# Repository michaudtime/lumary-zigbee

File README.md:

# Lumary Zigbee Controller

Replaces the Tuya WiFi controller inside a **Lumary 6" RGBAI recessed light** with an **ESP32-H2 Zigbee controller**, enabling:

- Direct Zigbee binding to Inovelli Blue Series switches (hub-independent on/off, dimming, scene control)
- 6 built-in lighting effects on the accent ring, with per-scene parameters stored on-device
- Zigbee OTA firmware updates via Zigbee2MQTT

## Hardware

| Component | Part |
|---|---|
| Controller | **lumary-brain rev A** — custom ESP32-H2-MINI-1 board, drop-in for the stock `KOK-AH-A172C` (see `hardware/`) |
| Target light | [Lumary Smart RGBAI Recessed Light 6"](https://www.lumarysmart.com/products/lumary-smart-recessed-light-with-gradient-auxiliary-light) |
| Switch | [Inovelli Blue Series 2-1 Zigbee](https://inovelli.com/products/zigbee-matter-blue-series-smart-2-1-on-off-dimmer-switch) |

### The two light sources

The fixture has two independent sources, and the firmware drives them as **two separate Zigbee
endpoints**, so Home Assistant sees two independent light entities rather than one:

| Source | Hardware | Driven by |
|---|---|---|
| Outer "gradient" ring | 62-pixel 5 V 3535 **RGBIC** strip, 3 colour bytes/pixel (no white die) | One data line, NZR over SPI |
| Inner white ring | 96 LEDs, 12 series × 4 parallel per colour, 2700 K + 6500 K | Two low-side PWM channels steering the driver's 380 mA |

The external `L-SD8E1` driver supplies **36.63 V constant-current** (inner white anode) and **4.7 V** (ring + logic). The board never sources the white current — it gates and steers it.

| Entity | Endpoint | Controls |
|---|---|---|
| `light.<name>_downlight` | 1 | on/off, brightness, colour temperature 2700–6500 K |
| `light.<name>_ring` | 2 | on/off, brightness, xy colour, the six effects |

> **Upgrading an already-paired fixture:** adding the second endpoint changes the device
> descriptor, and Zigbee2MQTT caches endpoints from the interview, so an already-paired fixture
> must be **re-interviewed** (Z2M frontend → device → Re-interview, or publish to
> `zigbee2mqtt/bridge/request/device/interview`) before the ring entity works. This has never been
> observed on hardware, so exactly what you'll see beforehand is unconfirmed either way -- expect
> the ring entity to be missing entirely, or present but unresponsive, until the re-interview is
> done. Newly paired fixtures just work.
>
> It is also no longer easy to check: both fixtures in service have already crossed this descriptor
> change, and a fixture that has crossed it cannot show you the before. Settling it would mean
> deliberately pairing a board on pre-2.0.0 firmware and upgrading it while watching -- worth doing
> when the remaining rev A boards are brought up, or this hedge should simply stay as written.

### Wiring (rev A board)

| ESP32-H2 Pin | Signal | Destination |
|---|---|---|
| GPIO 11 (SPI2 MOSI) | Ring data → 3.3→4.7 V buffer | `CN1.DIM` (ring DIN) |
| GPIO 4 | PWM cold white → Q1 gate | `CN1.CW-` (6500 K return) |
| GPIO 5 | PWM warm white → Q2 gate | `CN1.WW-` (2700 K return) |
| GPIO 9 | BOOT button | Bench download / BLE OTA |

> **Pin note:** GPIO 2/3/8/9/25 are ESP32-H2 strapping pins. The white PWM channels use GPIO 4/5 on rev A so the MOSFET gate pulldowns can't hold a strapping pin low at reset — the Super Mini prototype's GPIO 2/3 assignment does not carry over.

> **Level shifting:** the ring runs on the 4.7 V rail, so its data line is buffered up from 3.3 V by a `74AHCT1G125` (AHCT accepts 3.3 V as a logic high).

## Why SPI instead of RMT for the ring?

On ESP32-H2, the RMT peripheral conflicts with the Zigbee radio. Instead, SPI2 bit-encodes the single-wire NZR protocol: each NZR bit becomes 3 SPI bits (`1 → 110`, `0 → 100`) at 2.4 MHz, producing a valid 800 kHz signal on MOSI. The encoder lives in `src/pixel_encode.h`, deliberately free of ESP-IDF headers so it can be unit-tested on the host.

## Built-in Effects

These belong to the **Accent Ring** entity only — the Downlight has no effects, just on/off,
brightness and colour temperature.

| # | Name | Description |
|---|---|---|
| 1 | Warm Gradient | Warm→cool sweep rotating around the ring |
| 2 | Color Gradient | Multi-hue gradient rotating around ring |
| 3 | Breathing | Outer ring pulses in/out |
| 4 | Color Cycle | Full HSV hue rotation |
| 5 | Chase | Single lit segment travels around ring |
| 6 | Nightlight | Dim warm white outer ring only |

> **Changed in this version:** `static_white` and `static_color` are gone from the effect list.
> White is now the separate Downlight entity, and a solid ring colour is `effect: none` with a
> colour set. Automations naming either of the two removed effects need updating. Stored scenes
> are reseeded automatically — the NVS schema version bump discards the old indices rather than
> misreading them.

## Switch Control (Hub-Independent)

| Inovelli action | Behavior |
|---|---|
| 1× tap | On/Off |
| Hold up/down | Brightness |
| 2× tap up | Next effect — **via hub automation**, see below |
| 2× tap down | Previous effect — **via hub automation** |

On/off and dimming use direct Zigbee binding — **no hub required**, and they keep working if the
coordinator is down. With two fixture endpoints, the switch binds to both:

```
Bind from the Inovelli's endpoint 2 (the paddle) to BOTH fixture endpoints,
clusters genOnOff and genLevelCtrl:

  switch ep2 -> fixture ep1   (downlight)
  switch ep2 -> fixture ep2   (accent ring)
```

One tap down turns both sources off; one tap up brings both back at their own levels and colours.
This works because the Inovelli sends discrete `On`/`Off` rather than `Toggle` — verified on the
hardware. Under `Toggle`, two endpoints that had drifted into different states would diverge
further on every tap instead of converging. "Downlight only" is a Home Assistant action rather
than a switch action; remove the second binding if you would rather the ring ignored the switch.

> **Effect stepping is not hub-independent, and cannot be.** The Inovelli's multi-tap events are
> manufacturer-specific and go to the coordinator rather than to a bound light, so nothing the
> light does could make 2× tap work over pure binding. The automation reads the current
> `effect_select` and writes the next one. Not yet verified end to end (plan Task 6.4).

## Selecting an effect

Effect selection rides a **manufacturer-specific cluster (`0xFC00`)**, because nothing standard can
carry it: the Scenes cluster stores colour and level but knows nothing about an effect type, and
the Identify trigger-effects have no hook in the Arduino Zigbee library.

Install [`z2m/lumary-brain-revA.js`](z2m/lumary-brain-revA.js) into Z2M's `data/external_converters/`
and restart. Without the converter the light still works normally — the effects are simply
unreachable.

The converter exposes the effects as the **Accent Ring entity's native Home Assistant effect
list**, so they appear in the effect dropdown of the ring's light card itself rather than as a
separate entity:

```yaml
service: light.turn_on
target: {entity_id: light.lumary_kitchen_ring}
data: {effect: color_cycle}
```

That also means HA scene snapshots capture the running effect, and voice assistants can select one.
The current effect reads back as `state_attr('light.lumary_kitchen_ring', 'effect')`.

| Value | Meaning |
|---|---|
| `warm_gradient` … `nightlight` | One of the six built-in effects, in `EffectType` order |
| `none` | Not running an effect — showing a plain colour |

Setting a colour on the ring **exits the effect** and shows that colour instead, which reads back
as `none`. Selecting `none` does the same thing without changing the colour. Brightness continues
to scale whatever effect is running.

The selected effect persists across power cuts (NVS); `none` deliberately does not, so a power
cycle comes back to the stored effect.

> The Identify trigger-effects that Z2M's stock `effect` dropdown drives (`blink`, `breathe`,
> `okay`, …) are **switched off** in the converter, along with `power_on_behavior`. Both are on by
> default in `light()`, and this firmware implements neither — leaving them on would put controls in
> the light card that quietly do nothing. See `effect: false` / `powerOnBehavior: false` there.

> **Stepping through effects from the wall switch** is done by a hub automation, not by the light:
> read the current effect and set the next one. The Inovelli's multi-tap events go to the
> coordinator rather than to a bound light, so a hub is in the loop regardless.

Scene *storage* exists — 16 NVS slots, seeded with the defaults in `src/effect_params.h` — but
editing them is **not implemented**. There is no Add Scene support; `scene_store_save()` is only
called to seed defaults at first boot. Changing an effect's colour, speed or brightness
permanently is a future change.

## OTA Updates

> **Re-flashing a fixture that was already paired?** See "Upgrading an already-paired fixture"
> above — after this update it needs a Z2M **re-interview** before the ring entity works, or the
> upgrade will look broken even though it succeeded.

**Primary:** Zigbee OTA via Zigbee2MQTT.

Three things must all be true, and each one fails differently:

| Requirement | Symptom when missing |
|---|---|
| Firmware registers an OTA client | Device never asks; nothing in the Z2M log |
| Converter declares `ota: true` | **No `update` entity at all** in Home Assistant |
| Z2M can find the image via an index | Update entity exists; update fails `No image currently available` |

> **Z2M does not discover firmware by scanning a folder.** Copying a `.zigbee` file into `data/ota/`
> accomplishes nothing on its own — Z2M reads an *index* that describes the image, pointed at by
> `ota.zigbee_ota_override_index_location` in `configuration.yaml`. `scripts/gen-ota-index.py`
> generates one; see "Building an OTA image" below.

> **`ota` is a definition property, not a modern extend.** There is no `m.ota()` in
> zigbee-herdsman-converters, and using one makes Z2M reject the entire converter as invalid at load
> time. It goes on the definition object alongside `onEvent`.

**There is no fallback.** A BLE OTA path was planned — `PIN_BLE_OTA_BUTTON` is still defined in
`src/config.h` — but it was never implemented, and nothing references that pin. Do not count on it
for a fixture already in the ceiling: if Zigbee OTA cannot reach a light, the only recovery is
physical access to the USB port. Getting Zigbee OTA verified from an installed location is
consequently the gate on signing off the board (plan task 6.4), not a nice-to-have.

### Scheduled updates and automatic recovery (2.1.0 and later)

**Start updates with *schedule*, not *update*:**

```
topic:   zigbee2mqtt/bridge/request/device/ota_update/schedule
payload: {"id": "Loft Overhead Light"}
```

> **This means not using the Install button on Home Assistant's update card.** That button is the
> `ota_update/update` path: Zigbee2MQTT pushes an image notify at the fixture and waits for it to
> answer, which for a fixture a floor away from the coordinator typically ends in
> `OTA update of '<name>' failed (Device didn't respond to OTA request)` — a failure that says
> nothing about the image or the index. `schedule` parks the request instead and lets the fixture
> collect it on its own next query, which is what the recovery loop below is built around. Seen
> 2026-09-21 on the loft fixture: Install failed this way, the same image then installed from a
> schedule.
>
> `check`, `update` and `schedule` share one per-device lock, so a `schedule` sent while either of
> the others is still running is rejected with
> `OTA update or check for update already in progress for '<name>'`. Wait for the first to finish
> and send it again.

The fixture queries for an image shortly after it joins the network at boot, then hourly. A
scheduled update starts on whichever of those queries comes next, and Zigbee2MQTT keeps it
scheduled if it fails. Combined with the firmware's recovery this makes an update self-healing:

1. If a download aborts, or stalls for 3 minutes, the fixture saves its light state, restarts
   (the light blinks for about a second, then comes back as it was), and rejoins.
2. On rejoin it queries for an image, and the still-scheduled update starts again from the
   beginning.
3. When it succeeds, the fixture restarts into the new version and comes back **off** -- light
   state is only carried across a recovery restart, not across the update's own restart -- and
   Zigbee2MQTT clears the schedule.

The restart itself backs off on repeated recoveries: the first two consecutive recoveries restart
at once, but from the third the restart waits 5 minutes, doubling each time up to an hour, so an
image that fails the same way every time cannot make a fixture blink every few seconds. It never
stops retrying on its own -- `unschedule` is what stops it.

The restart is required: the Arduino Zigbee library never resets its OTA state after an abort, so
without it every retry fails `INVALID_IMAGE` two blocks in. To stop a fixture retrying an image that
can never succeed, send the same payload to `.../ota_update/unschedule`. Each recovery is logged on
the serial console with a running count.

**Fixtures on firmware older than 2.1.0** have no automatic recovery: after a failed update, power-
cycle the fixture before retrying. From Home Assistant, via its Inovelli switch: turn the switch
off, set its Smart Bulb Mode to `Disabled` (the switch is off, so the load loses power), wait ~15 s,
then set Smart Bulb Mode back to `Smart Bulb Mode` (full power returns and the fixture boots).

### Building an OTA image

The device registers an OTA client at startup and queries for an image once it
joins, then hourly. The coordinator only offers images numbered **above** the
running version, so the version block in `src/version.h` must be bumped and the
same `ZB_FW_VERSION` passed as `--file-version` below — if they disagree, the
update silently never appears.

> **The tool was renamed and its CLI changed.** Espressif's `tools/ota_image_tool.py`
> is gone; it is now `tools/image_builder_tool/image_builder_tool.py`, it takes short
> flags rather than the old long ones, and the firmware is supplied as a `--tag`
> sub-element rather than a positional argument. There is no `create` subcommand, and
> the output filename is generated for you rather than given. Verified 2026-08-18.

```bash
# Get the tool
mkdir -p build/ota && curl -sSL -o build/ota/image_builder_tool.py   https://raw.githubusercontent.com/espressif/esp-zigbee-sdk/main/tools/image_builder_tool/image_builder_tool.py

# Build firmware (bump the version block in src/version.h first)
pio run -e esp32h2

# Wrap as an OTA image. -m/-i come from src/config.h (ZB_MANUFACTURER_CODE,
# ZB_IMAGE_TYPE); -v must equal ZB_FW_VERSION. Tag 0x0000 is the upgrade image.
cd build/ota && python image_builder_tool.py   -m 0x1001   -i 0x0001   -v 0x02000000   -s 2   -g "LumaryZigbee"   --tag 0x0000 ../../.pio/build/esp32h2/firmware.bin
```

The output is named from the three identifiers rather than chosen — for the values above,
`1001-0001-02000000-ota-file.zigbee`.

Then generate the index Z2M actually reads. It takes the manufacturer code, image type, file version
and header string out of the image itself rather than from arguments, so the index cannot disagree
with the file it describes:

```bash
python scripts/gen-ota-index.py build/ota/1001-0001-02000000-ota-file.zigbee
```

Copy **both** the `.zigbee` image and the generated `index.json` into Z2M's `data/ota/` folder, then
point `configuration.yaml` at the index and restart Z2M:

```yaml
ota:
  zigbee_ota_override_index_location: ota/index.json
```

Both paths are relative to the **Z2M data directory** — the index's own location, and the `url`
inside it naming the image. Verified end to end 2026-08-18 against Z2M 2.13.0: no http(s) URL and no
absolute path is needed for a locally served image.

> **The `url` is relative to the data directory, not to the index that contains it.** With the
> layout above the index lives at `data/ota/index.json` and the image sits beside it, so the `url`
> still needs the `ota/` prefix — `ota/foo.zigbee`, not `foo.zigbee`. `gen-ota-index.py` adds it.
>
> Getting this wrong is worth recognising, because it does not look like a path problem.
> `ota_update/check` reads index *metadata* only, so it reports `update_available: true` and Home
> Assistant offers the update quite happily. Only `ota_update/update` opens the file, and it reports
> the failure as **`No image currently available`** — the same message you get with no index at all.
> The real cause appears only in Z2M's debug log:
>
> ```
> zh:controller:ota: Reading firmware image from 'foo.zigbee'
> ENOENT: no such file or directory, open '/config/zigbee2mqtt/foo.zigbee'
> ```

Z2M caches the last OTA check, so after installing an index it will keep reporting the device as up
to date until it re-checks — on the next device announce, hourly, or immediately if you ask:

```
topic:   zigbee2mqtt/bridge/request/device/ota_update/check
payload: {"id": "Overhead light test"}
```

For a one-off test you can skip the index entirely and name the file in the update request, which is
useful for confirming the image itself is good before troubleshooting configuration:

```
topic:   zigbee2mqtt/bridge/request/device/ota_update/update
payload: {"id": "Overhead light test", "url": "ota/1001-0001-02000000-ota-file.zigbee"}
```

`build/` is git-ignored, so neither the tool, the image, nor the index is committed.

## Build & Flash

> **Re-flashing a fixture that was already paired?** See "Upgrading an already-paired fixture"
> above — after this update it needs a Z2M **re-interview** before the ring entity works, or the
> upgrade will look broken even though it succeeded.

> **Windows:** run `pio` from **PowerShell or cmd**, not Git Bash. This platform
> version installs its toolchain via `idf_tools.py`, which aborts with
> `ERROR: MSys/Mingw is not supported` under Git Bash. Building also needs
> Windows long-path support enabled (`LongPathsEnabled = 1`).
>
> `--target upload` fails differently and much more confusingly under Git Bash:
> esptool's progress bar is drawn with box-drawing characters, stdout falls back
> to **cp1252**, and the whole upload dies on `UnicodeEncodeError: 'charmap'
> codec can't encode characters` — after sitting silent for ~6 minutes, with the
> traceback replacing whatever the real error was. The board is fine; nothing was
> written. From PowerShell the same flash takes ~18 s. If you must run it from a
> shell with a non-UTF-8 codepage, `chcp 65001` and `PYTHONIOENCODING=utf-8`
> clear it (observed 2026-09-21).

```bash
# Install PlatformIO CLI if needed
pip install platformio

# Build
pio run -e esp32h2

# Flash
pio run -e esp32h2 --target upload

# Serial monitor
pio device monitor
```

## Project Structure

```
src/
  config.h          — Pin definitions, constants
  color.h           — CRGB struct, HSV conversion, color math
  pixel_encode.h    — NZR-over-SPI bit encoder (hardware-free, unit-tested)
  led_driver.h/.cpp — SPI2 ring driver + LEDC CW/WW PWM
  effect_params.h   — EffectType enum, EffectParams struct
  effects.h/.cpp    — 6 effect implementations + lookup table
  scene_store.h/.cpp — NVS scene persistence
  zigbee_light.h/.cpp — Zigbee clusters for both endpoints, and the OTA client
  brightness.h      — CIE 1931 lightness curve, generated tables
  main.cpp          — Setup, loop, watchdog
test/
  test_brightness/   — Host unit tests for the perceptual curve
  test_identify/     — Host unit tests for the identify overlay
  test_light_state/  — Host unit tests for the Zigbee -> fixture translation
  test_pixel_encode/ — Host unit tests for pixel encoding + color math
  test_version/      — Host unit tests for the version block
z2m/
  lumary-brain-revA.js — Z2M external converter
  test/             — Converter tests (stubbed, `node z2m/test/converter.test.mjs`)
hardware/
  kicad/            — Board design (build_board.py generates the .kicad_pcb)
  bom.csv, calcs.md, schematic-nets.md
docs/
  spec.md           — Hardware + software design specification
  plan.md           — Implementation plan
  superpowers/      — Board replacement spec, plan, and Phase 0 measurements
```

## Tests

Hardware-independent logic (pixel encoding, colour math) has host-side unit tests:

```bash
scripts\run-native-tests.bat
```

> PlatformIO's `platform = native` expects a gcc toolchain; this script compiles the
> same tests with the MSVC Build Tools that are installed instead. `pio test -e native`
> works as-is on a machine with gcc.

The Z2M converter has its own suite, covering the effect names, their wire indices and the
exposes Home Assistant discovers from them. It stubs the `zigbee-herdsman-converters` imports,
so it needs nothing installed but Node:

```bash
node z2m/test/converter.test.mjs
```

## Status

- [x] Design spec
- [x] Implementation plan
- [x] Task 1: Project scaffold
- [x] Task 2: Color utilities
- [x] Task 3: LED driver
- [x] Task 4: Scene storage
- [x] Task 5: Effects engine
- [x] Task 6: Zigbee basics
- [x] Task 7: Zigbee color + effect selection
- [x] Task 8: Zigbee OTA
- [ ] Task 9: BLE OTA fallback -- won't do (decided 2026-08-19); see "OTA Updates" above
- [ ] Task 10: Integration + validation -- bench-verified end to end
      (`docs/superpowers/plans/2026-08-18-bench-verification.md`, §§1-9), and **signed off from an
      installed ceiling location 2026-09-19**: binding to the Inovelli confirmed from the loft at
      LQI 126-138, and a real over-the-air update completed from there (Task 6.4 in
      `docs/superpowers/plans/2026-08-01-brain-replacement-board.md`). Still open: the
      already-paired-fixture upgrade path -- see the note under "Two entities" above, which now
      needs a fixture deliberately left on pre-2.0.0 firmware to observe at all
      (RSSI, thermals, a real OTA from there)

## License

MIT

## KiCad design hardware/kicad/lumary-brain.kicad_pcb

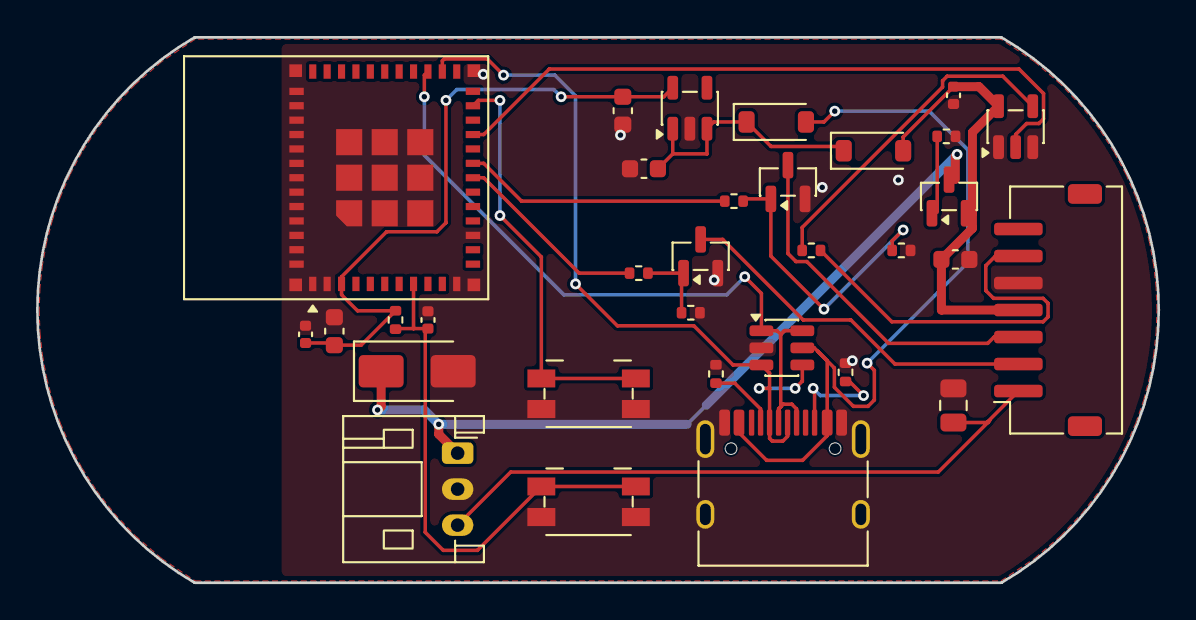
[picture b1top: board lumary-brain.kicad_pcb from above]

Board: 2 copper layers, 62.3 x 30.3 mm, 32 parts (0 on the bottom side), 23 nets.

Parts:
C1: 10uF/50V; C_0805_2012Metric
C2, C4, C5: 10uF; C_0603_1608Metric
C3: 1uF; C_0603_1608Metric
C6, C7: 100nF; C_0402_1005Metric
C8: 1uF; C_0402_1005Metric
D1, D2: B5819W; D_SOD-123
D3: SMAJ5.0A; D_SMA
J1: PWR_IN; JST_PH_S3B-PH-K_1x03_P2.00mm_Horizontal
J2: CN1; JST_ZH_S7B-ZR-SM4A-TF_1x07-1MP_P1.50mm_Horizontal
J3: USB-C; USB_C_Receptacle_HRO_TYPE-C-31-M-12
Q1, Q2: NMOS_60V; SOT-23
Q3: AO3401A; SOT-23
R1, R2: 100R; R_0402_1005Metric
R3, R4, R9: 100k; R_0402_1005Metric
R5: 200R; R_0402_1005Metric
R6: 10k; R_0402_1005Metric
R7, R8: 5.1k; R_0402_1005Metric
SW1: BOOT; Panasonic_EVQPUJ_EVQPUA
SW2: EN; Panasonic_EVQPUJ_EVQPUA
U1: ESP32-H2-MINI-1-N4; ESP32-C6-MINI-1
U2: ME6211C33M5G; SOT-23-5
U3: 74AHCT1G125; SOT-23-5
U4: USBLC6-2SC6; SOT-23-6

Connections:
+3V3: C2.1, C5.1, C6.1, R6.2, U1.3, U2.5
+4V7: C4.1, C7.1, D1.2, J2.4, Q3.2, U3.5
+4V7_IN: D3.1, J1.1, Q3.3
+36V: C1.1, J1.3, J2.1
CC1: J3.A5, R7.1
CC2: J3.B5, R8.1
CW_GATE: Q1.1, R1.2, R3.1
CW_PWM: R1.1, U1.18
CW_RET: J2.2, Q1.3
EN: C8.1, R6.1, SW2.1, U1.8
GND: C1.2, C2.2, C3.2, C4.2, C5.2, C6.2, C7.2, C8.2, D3.2, J1.2, J2.5, J3.A1, J3.A12, J3.B1, J3.B12, J3.SH, Q1.2, Q2.2, R3.2, R4.2, R7.2, R8.2, R9.2, SW1.2, SW2.2, U1.1, U1.2, U1.11, U1.14, U1.36, U1.37, U1.38, U1.39, U1.40, U1.41, U1.42, U1.43, U1.44, U1.45, U1.46, U1.47, U1.48, U1.49, U1.50, U1.51, U1.52, U1.53, U2.2, U3.1, U3.3, U4.2
IO9: SW1.1, U1.23
LDO_IN: C3.1, D1.1, D2.1, U2.1, U2.3
Q3_GATE: Q3.1, R9.1
RING_BUF_OUT: R5.1, U3.4
RING_DATA: J2.6, R5.2
RING_DATA_3V3: U1.21, U3.2
USB_DM: J3.A7, J3.B7, U1.26, U4.3, U4.4
USB_DP: J3.A6, J3.B6, U1.27, U4.1, U4.6
VBUS: D2.2, J3.A4, J3.A9, J3.B4, J3.B9, U4.5
WW_GATE: Q2.1, R2.2, R4.1
WW_PWM: R2.1, U1.19
WW_RET: J2.3, Q2.3

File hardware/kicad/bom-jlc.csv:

Comment,Designator,Footprint,LCSC Part #
10uF 50V,C1,0805,C440198
10uF 10V+,"C2,C4,C5",0603,C19702
1uF,C3,0603,C15849
100nF,"C6,C7",0402,C1525
1uF,C8,0402,C52923
B5819W SL,"D1,D2",SOD-123,C8598
SMAJ5.0A,D3,SMA,C113952
S3B-PH-K-S(LF)(SN),J1,JST-PH-3,C157929
S7B-ZR-SM4A-TF(LF)(SN),J2,ZH-7-SIDE,C5118704
TYPE-C-31-M-12 USB-C,J3,USB-C-16P,C165948
N-MOSFET 60V logic-level,"Q1,Q2",SOT-23,C347492
AO3401A,Q3,SOT-23,C15127
100R,"R1,R2",0402,C25076
100k,"R3,R4,R9",0402,C25741
200R,R5,0402,C25087
10k,R6,0402,C60489
5.1k,"R7,R8",0402,C25905
Tact switch EVQPUJ/EVQPUA,"SW1,SW2",SMD-4.7x3.5,C128539
ESP32-H2-MINI-1-N4,U1,ESP32-H2-MINI-1,C18203134
ME6211C33M5G-N,U2,SOT-23-5,C82942
SN74AHCT1G125DBVR,U3,SOT-23-5,C7484
USBLC6-2SC6,U4,SOT-23-6,C7519

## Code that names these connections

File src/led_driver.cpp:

#include "led_driver.h"
#include "pixel_encode.h"
#include "driver/spi_master.h"
#include "driver/ledc.h"

static spi_device_handle_t s_spi;
static uint8_t s_spi_buf[RING_SPI_BUF_SIZE];

void led_driver_init() {
    spi_bus_config_t bus = {};
    bus.mosi_io_num    = PIN_RING_DATA;
    bus.miso_io_num    = -1;
    bus.sclk_io_num    = PIN_RING_CLK_DUMMY;
    bus.quadwp_io_num  = -1;
    bus.quadhd_io_num  = -1;
    bus.max_transfer_sz = RING_SPI_BUF_SIZE;
    ESP_ERROR_CHECK(spi_bus_initialize(SPI2_HOST, &bus, SPI_DMA_CH_AUTO));

    spi_device_interface_config_t dev = {};
    dev.clock_speed_hz = RING_SPI_CLK_HZ;
    dev.mode           = 0;
    dev.spics_io_num   = -1;
    dev.queue_size     = 1;
    ESP_ERROR_CHECK(spi_bus_add_device(SPI2_HOST, &dev, &s_spi));

    ledc_timer_config_t timer = {};
    timer.speed_mode      = LEDC_LOW_SPEED_MODE;
    timer.timer_num       = LEDC_TIMER_0;
    timer.duty_resolution = PWM_RESOLUTION;
    timer.freq_hz         = PWM_FREQ_HZ;
    timer.clk_cfg         = LEDC_AUTO_CLK;
    ESP_ERROR_CHECK(ledc_timer_config(&timer));

    ledc_channel_config_t cw = {};
    cw.gpio_num   = PIN_CW_PWM;
    cw.speed_mode = LEDC_LOW_SPEED_MODE;
    cw.channel    = PWM_CHANNEL_CW;
    cw.timer_sel  = LEDC_TIMER_0;
    cw.duty       = 0;
    ESP_ERROR_CHECK(ledc_channel_config(&cw));

    ledc_channel_config_t ww = cw;
    ww.gpio_num = PIN_WW_PWM;
    ww.channel  = PWM_CHANNEL_WW;
    ESP_ERROR_CHECK(ledc_channel_config(&ww));
}

void led_driver_show(const CRGB* leds, uint16_t count) {
    memset(s_spi_buf, 0, RING_SPI_LEAD_BYTES);
    pixel_encode(leds, count, s_spi_buf + RING_SPI_LEAD_BYTES,
                 RING_SPI_BUF_SIZE - RING_SPI_LEAD_BYTES);
    spi_transaction_t t = {};
    t.length    = RING_SPI_BUF_SIZE * 8;
    t.tx_buffer = s_spi_buf;
    spi_device_polling_transmit(s_spi, &t);
}

void led_driver_set_cw(uint16_t duty) {
    ledc_set_duty(LEDC_LOW_SPEED_MODE, PWM_CHANNEL_CW, duty > PWM_DUTY_MAX ? PWM_DUTY_MAX : duty);
    ledc_update_duty(LEDC_LOW_SPEED_MODE, PWM_CHANNEL_CW);
}

void led_driver_set_ww(uint16_t duty) {
    ledc_set_duty(LEDC_LOW_SPEED_MODE, PWM_CHANNEL_WW, duty > PWM_DUTY_MAX ? PWM_DUTY_MAX : duty);
    ledc_update_duty(LEDC_LOW_SPEED_MODE, PWM_CHANNEL_WW);
}

void led_driver_off() {
    static const CRGB black[RING_NUM_LEDS] = {};
    led_driver_show(black, RING_NUM_LEDS);
    led_driver_set_cw(0);
    led_driver_set_ww(0);
}

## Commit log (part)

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2026-04-18 fix: pin arduino-esp32 3.1.3 for ESP32-H2 board support
2026-04-18 fix: switch to pioarduino platform for ESP32-H2 Arduino support
2026-04-18 fix: use correct ESP32-H2 board ID esp32-h2-devkitm-1
2026-04-18 feat: add color utils, LED driver, scene store, effects engine, bench test main
2026-04-18 debug: minimal serial test
2026-04-18 debug: remove ZIGBEE_MODE_ED to isolate serial boot issue
2026-04-18 debug: wait for USB CDC host before printing
2026-04-18 fix: enable USB CDC for ESP32-H2 Super Mini native USB
2026-04-18 feat: restore LED driver and effects bench test
